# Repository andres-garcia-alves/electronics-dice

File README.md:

# Electronic-Dice

Arduino &amp; PIC16F84A source code & building details for an electronic dice (with animations). 

Available animations:
- #01: corner leds followed by the central one
- #02: perimeter leds followed by the central one
- #03: loop row-by-row from upper to bottom
- #04: bounce row-by-row from upper to bottom
- #05: go one-by-one over leds perimeter
- #06: a dot going in horizontal lines
- #07: a dot going in vertical lines
- #08: a dot going in zig-zag
- #09: loop of horizontal and vertical lines
- #10: a dot going in vertical lines followed by horizontal ones
- #11: random dots
- #12: random dots fill
- #13: random dot fill & random dot empty

&nbsp;

This project use the following electronic components:
-  1 x Arduino UNO / Nano v3
-  1 x push-button
-  1 x switch-button
-  7 x red LEDs
-  7 x 330 ohm resistors
-  1 x ON/OFF button
-  1 x blue LED
-  1 x 10k ohm resistor
-  1 x experimental board (single face) 6x8cm
-  1 x experimental board (double face) 6x8cm
-  1 x 9v battery
-  1 x small plastic box
- 10 x short female wires
- 20 x male 90 degrees pins

The circuit:
- Dice button attached to pin 2
- Switch button attached to pin 3 (enable/disable animations)
- Red LEDs attached to pins 4-10 (see code comments for details)

Pinout:

      *(A)        *(B)

      *(C)  *(D)  *(E)

      *(F)        *(G)

  - D02 -> input with button interrupt
  - D03 -> input with switch
  - D04 -> output to bottom-right led (G)
  - D05 -> output to middle-right led (E)
  - D06 -> output to upper-right led (B)
  - D07 -> output to middle-center led (D)
  - D08 -> output to bottom-left led (F)
  - D09 -> output to middle-left led (C)
  - D10 -> output to upper-left led (A)

&nbsp;

### Screenshots

| Schematics                               | PCB Layout                               |
|------------------------------------------|------------------------------------------|
|   |          |

| PCB 3D Render                            | PCB 3D Render                            |
|------------------------------------------|------------------------------------------|
|    |    |

| Prototype                                |  Prototype                               |
|------------------------------------------|------------------------------------------|
|        |        |

| Building                                 |  Building                                |
|------------------------------------------|------------------------------------------|
|         |         |

| Building                                 |  Building                                |
|------------------------------------------|------------------------------------------|
|         |         |

| Project Final                            | Project Final (YouTube video)            |
|------------------------------------------|------------------------------------------|
|         |  |

See 'Rescources' sub-folder for more pictures & videos of the project.

&nbsp;

### Version History

v1.0 (2022.02.23) - Initial release.  
v1.1 (2022.02.24) - Adding ON/OFF animations switch. Fixed bug with random secuences (randomSeed).  
v1.2 (2022.02.27) - Re-arrange LEDs pin-out to simplify PCB.  
v1.3 (2022.03.09) - Animations improved with ROM tables: line count 622->342 (compiled size reduced by 20%).  
v1.4 (2022.03.10) - Dice number improved with masked bits: line count 342 -> 296.  
v1.5 (2025.12.26) - Adding KiCAD 9 schematics and PCB diagrams.

&nbsp;

This source code is licensed under GPL v3.0  
Please send me your feedback about this project: andres.garcia.alves@gmail.com

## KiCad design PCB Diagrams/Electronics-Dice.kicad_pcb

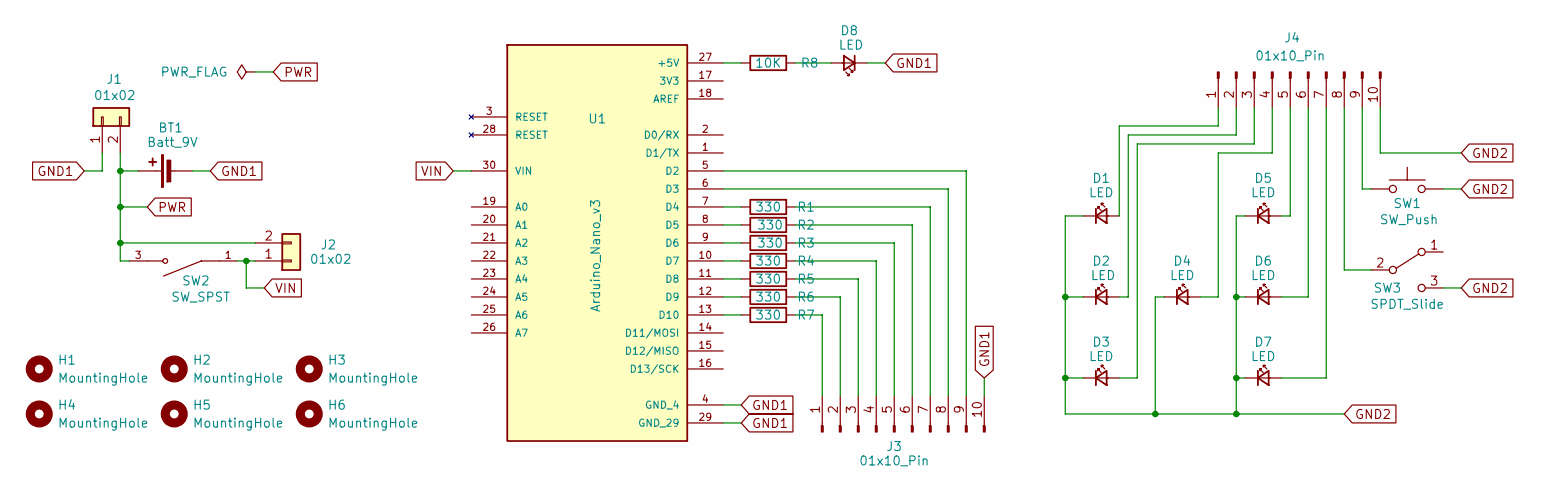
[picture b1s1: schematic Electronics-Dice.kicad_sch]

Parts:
BT1: Batt_9V; BatteryHolder_Eagle_12BH611-GR
D1, D2, D3, D4, D5, D6, D7: LED; LED_D5.0mm
D8: LED; LED_D3.0mm
H1, H2, H3, H4, H5, H6: MountingHole; MountingHole_2mm
J1, J2: 01x02; PinHeader_1x02_P2.54mm_Vertical
J3, J4: 01x10_Pin; PinHeader_1x10_P2.54mm_Vertical
R1, R2, R3, R4, R5, R6, R7: 330; R_Axial_DIN0204_L3.6mm_D1.6mm_P5.08mm_Horizontal
R8: 10K; R_Axial_DIN0204_L3.6mm_D1.6mm_P7.62mm_Horizontal
SW1: SW_Push; SW_PUSH_6mm_H9.5mm
SW2: SW_SPST; Push_Button_Switch_THT_C&K_D6R90LGS
SW3: SPDT_Slide; Slide_SPDT_PTH_11.6x4.0mm
U1: Arduino_Nano_v3

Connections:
GND1: BT1.2 (-), D8.1 (K), J1.1, J3.10, U1.4 (GND_4), U1.29 (GND_29)
GND2: D1.1 (K), D2.1 (K), D3.1 (K), D4.1 (K), D5.1 (K), D6.1 (K), D7.1 (K), J4.10, SW1.2, SW3.3 (C)
unnamed: D1.2 (A), J4.1
unnamed: D2.2 (A), J4.2
unnamed: D3.2 (A), J4.3
unnamed: D4.2 (A), J4.4
unnamed: D5.2 (A), J4.5
unnamed: D6.2 (A), J4.6
unnamed: D7.2 (A), J4.7
unnamed: D8.2 (A), R8.2
unnamed: J3.1, R7.2
unnamed: J3.2, R6.2
unnamed: J3.3, R5.2
unnamed: J3.4, R4.2
unnamed: J3.5, R3.2
unnamed: J3.6, R2.2
unnamed: J3.7, R1.2
unnamed: J3.8, U1.6 (D3)
unnamed: J3.9, U1.5 (D2)
unnamed: J4.8, SW3.2 (B)
unnamed: J4.9, SW1.1
unnamed: R8.1, U1.27 (+5V)
unnamed: R1.1, U1.7 (D4)
unnamed: R2.1, U1.8 (D5)
unnamed: R3.1, U1.9 (D6)
unnamed: R4.1, U1.10 (D7)
unnamed: R5.1, U1.11 (D8)
unnamed: R6.1, U1.12 (D9)
unnamed: R7.1, U1.13 (D10)
PWR: BT1.1 (+), J1.2, J2.2, SW2.3, SW2.4
VIN: J2.1, SW2.1, SW2.2, U1.30 (VIN)

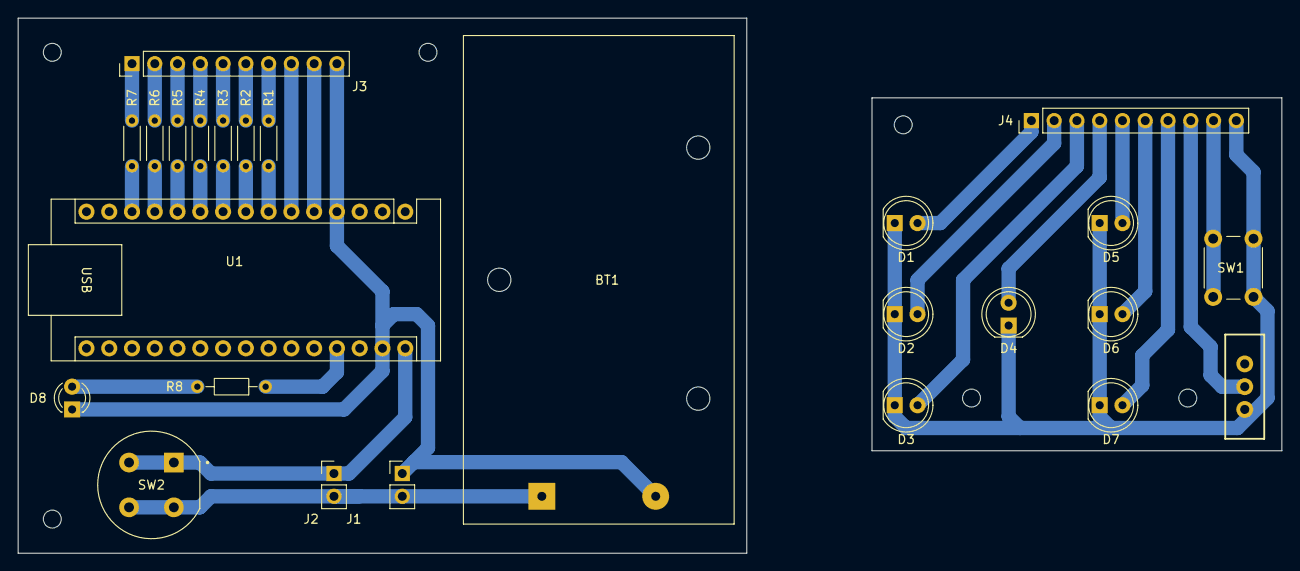
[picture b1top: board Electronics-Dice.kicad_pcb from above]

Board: 2 copper layers, 141.0 x 59.7 mm, 31 parts (0 on the bottom side), 31 nets.

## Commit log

2022-03-10 improvement of animations code with ROM tables
2022-03-10 animations improvement using ROM tables
2022-03-10 dice number improvement using masked bits
2022-03-10 readme update
2022-03-17 Create LICENSE
2023-07-06 update Resources folder
2025-12-26 Adding KiCAD 9 schematics and PCB diagrams
